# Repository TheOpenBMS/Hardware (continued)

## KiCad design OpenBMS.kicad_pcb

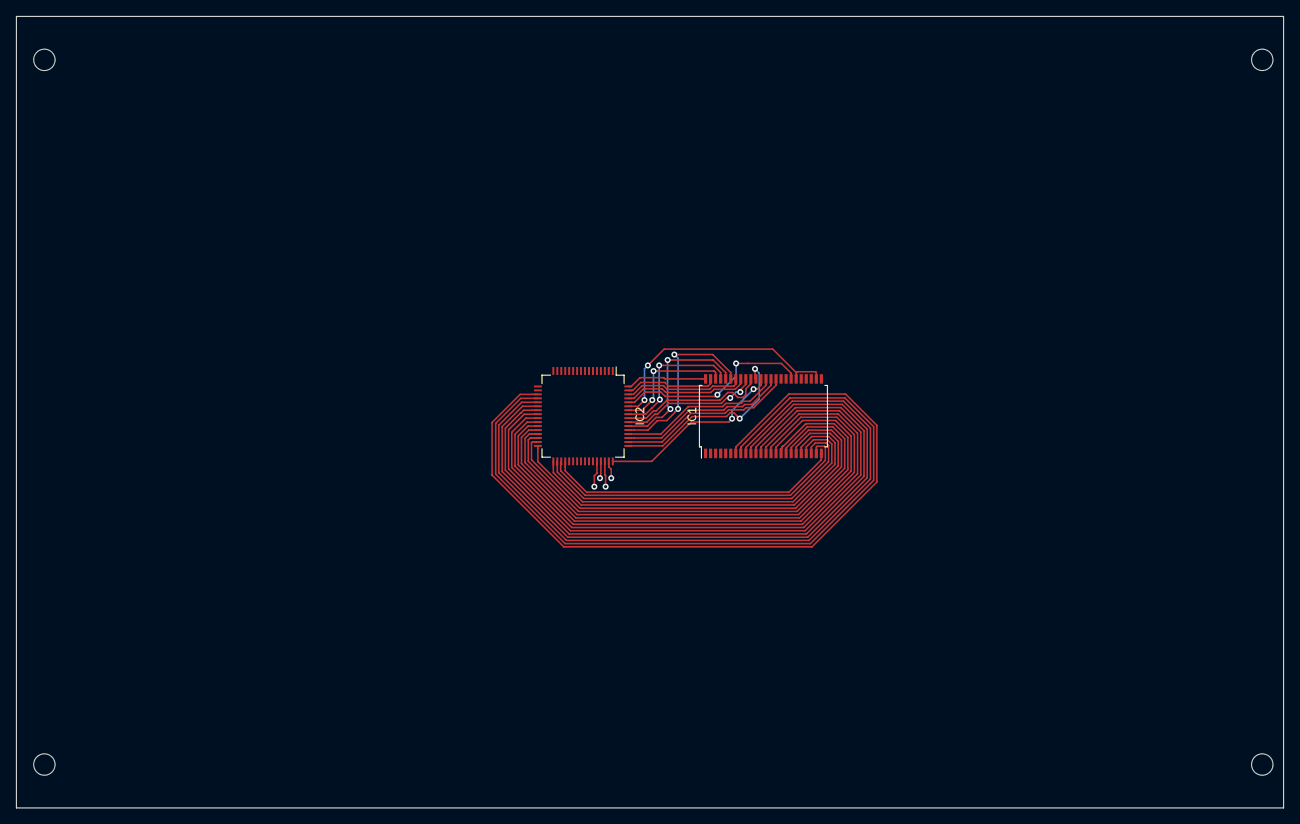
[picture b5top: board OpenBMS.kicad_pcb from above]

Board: 4 copper layers, 159.9 x 99.9 mm, 6 parts (0 on the bottom side), 47 nets.

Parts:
IC1: LTC6811-1; SSOP-48_7.5x15.9mm_P0.635mm
IC2: LTC6813ILWE-1#3ZZPBF; LQFP-64_10x10mm_P0.5mm
MK1, MK2, MK3, MK4: Mounting_Hole_PAD; MountingHole_2.7mm

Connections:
C0: IC1.26, IC1.30, IC2.38, IC2.59
C1: IC1.24, IC2.36
C2: IC1.22, IC2.34
C3: IC1.20, IC2.32
C4: IC1.18, IC2.30
C5: IC1.16, IC2.28
C6: IC1.14, IC2.26
C7: IC1.12, IC2.24
C8: IC1.10, IC2.22
C9: IC1.8, IC2.20
C10: IC1.6, IC2.18
C11: IC1.4, IC2.16
C12: IC1.2, IC2.14
DRIVE: IC1.38, IC2.49
DTEN: IC1.36, IC2.52
GPIO1: IC1.27, IC2.39
GPIO2: IC1.28, IC2.40
GPIO3: IC1.29, IC2.41
GPIO4: IC1.32, IC2.42
GPIO5: IC1.33, IC2.43
IBIAS: IC1.45, IC2.57
ICMP: IC1.46, IC2.58
IMB: IC1.47, IC2.63
IPB: IC1.48, IC2.64
ISOMD: IC1.40, IC2.55
S1: IC1.25, IC2.37
S2: IC1.23, IC2.35
S3: IC1.21, IC2.33
S4: IC1.19, IC2.31
S5: IC1.17, IC2.29
S6: IC1.15, IC2.27
S7: IC1.13, IC2.25
S8: IC1.11, IC2.23
S9: IC1.9, IC2.21
S10: IC1.7, IC2.19
S11: IC1.5, IC2.17
S12: IC1.3, IC2.15
V2: IC1.31, IC2.60
V+: IC1.1, IC2.1
VREF1: IC1.35, IC2.51
VREF2: IC1.34, IC2.50
VREG: IC1.37, IC2.48
WDT: IC1.39, IC2.56
~CSB: IC1.41, IC2.61
~SCLK: IC1.42, IC2.62
~SDI: IC1.43, IC2.53
~SDO: IC1.44, IC2.54

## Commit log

2019-08-30 Add files via upload
    Standalone_Com_Shield.pro for review
2019-08-30 Add file via upload
    Added the LTC6811_12cell_DCARD directory and project. Missing a number of files, need to use CLI since the upload does not take sub-directories...
2019-08-30 pushing from CLI
2019-08-31 removing Stanadard_Interface.pro via CLI
2019-08-31 added Open Hardware Logo to Standalone_Com_Shield.kicad_pcb via CLI
2019-08-31 moved Shield designs to new directories - added via CLI
2019-08-31 updated Standalone_Shield SCH for BOM file - added via CLI
2019-09-04 generated PDFs for SCH and PCB - added via CLI
2019-09-16 Adding everything again - via CLI
2019-09-18 Adding 12 Cell IO board - via CLI
2019-09-20 adding 12 Cell IO - via CLI
